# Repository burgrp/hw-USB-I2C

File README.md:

# USB-I2C bridge

USB to I2C bridge implemented on ESP32-C3FN4 MCU.

## Features

- Serial to I2C interface
- Alert line
- 3.3V, 5V power supply
- Simple serial protocol
- Implemented in MicroPython
- Designed in KiCAD

## Connectors

All connectors have the same pin-out as follows.

1. GND
2. SCL
3. SDA
4. +3.3 V
5. +5V
6. ALERT (IRQ)

## Binding

For Node.js there is a library [i2c-js](https://github.com/burgrp/i2c-js) published on NPM as [@burgrp/i2c](https://www.npmjs.com/package/@burgrp/i2c).

## USB protocol

- VID: 303A
- PID: 1001

The bridge is controlled through serial port by simple text protocol:

- `S` scans bus for devices, replies `Saddr1,addr2,addr3,...`
- `R,addr,len` reads data from device, replies `R,hex_data`
- `W,addr,hex_data` writes data to device, replies `W,acked_count`
- `A` gets alert line status, replies `AT` (true) or `AF` (false).

Addresses are always expressed in 7bit format, therefore without R/W bit.

### Example

By commands `S`, `R,79,2`, `A` we can scan the bus, read temperature from LM75A sensor found on address 79 and check the alert line:

```
> miniterm /dev/ttyACM0 115200 --raw
--- Miniterm on /dev/ttyACM0  115200,8,N,1 ---
--- Quit: Ctrl+] | Menu: Ctrl+T | Help: Ctrl+T followed by Ctrl+H ---
S
S79
R,79,2
R1A40
A
AF
```

## License
This work is licensed under a Creative Commons Attribution-ShareAlike 4.0 International License.

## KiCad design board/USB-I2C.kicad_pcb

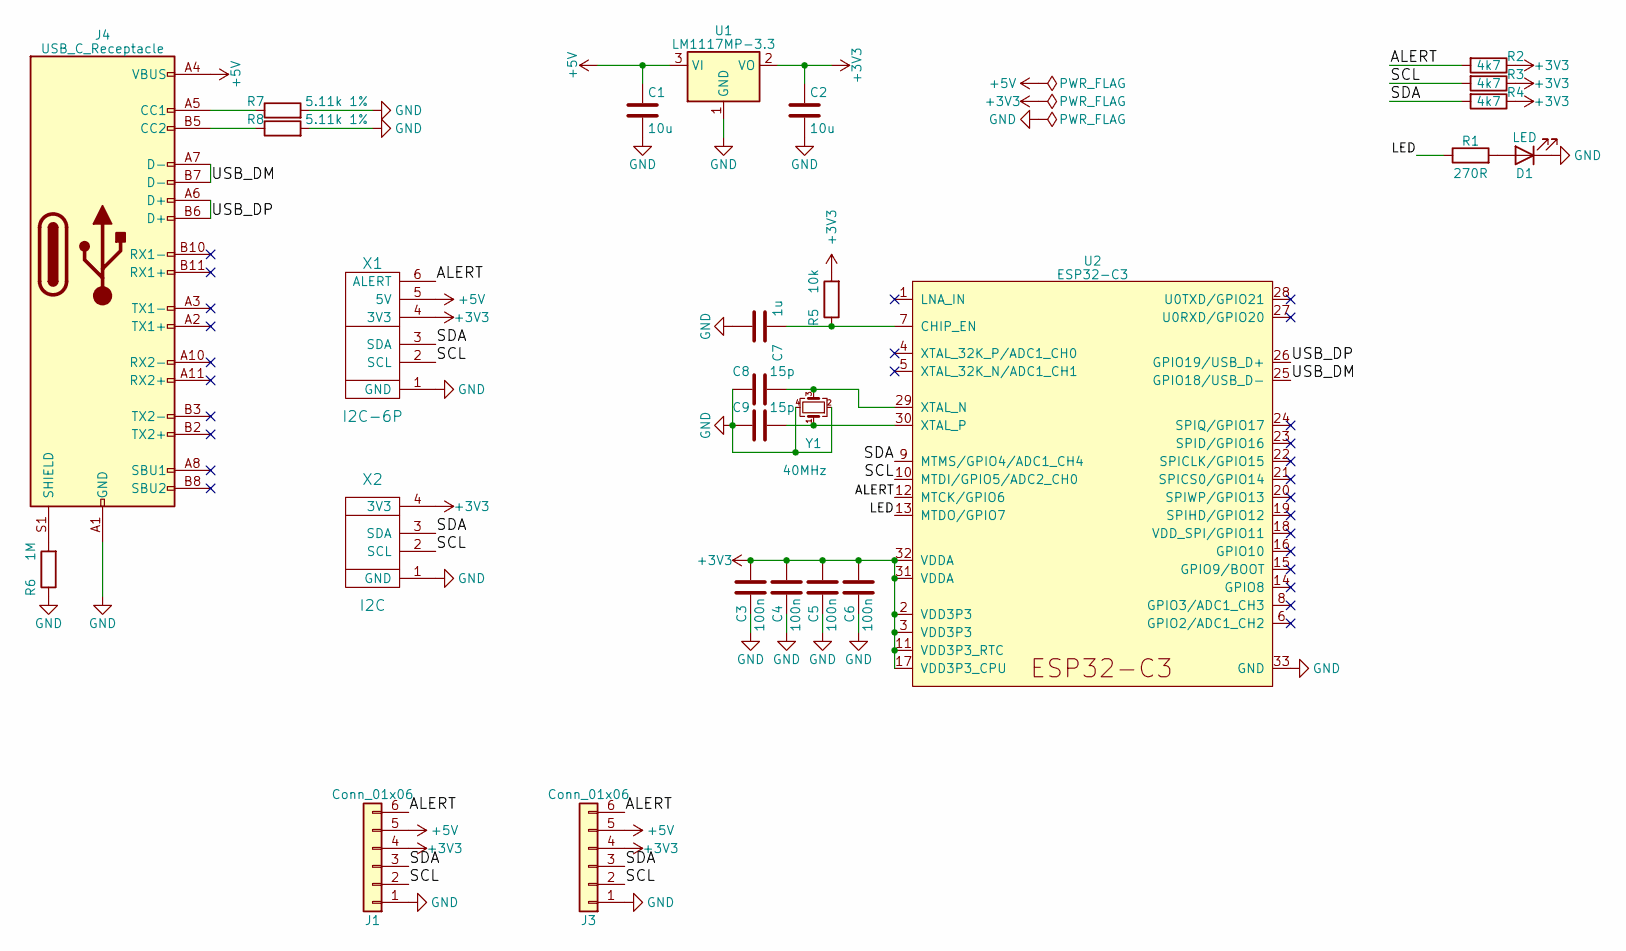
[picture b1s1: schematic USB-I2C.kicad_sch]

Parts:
C1, C2: 10u; C_0805_2012Metric
C3, C4, C5, C6: 100n; C_0805_2012Metric
C7: 1u; C_0805_2012Metric
C8, C9: 15p; C_0805_2012Metric
D1: LED; LED_0805_2012Metric
J1: Conn_01x06; PinHeader_1x06_P2.54mm_Vertical
J3: Conn_01x06; IDC-Header_2x03_P2.54mm_Vertical
J4: USB_C_Receptacle; USB_C_Receptacle_G-Switch_GT-USB-7010ASV
R1: 270R; R_0805_2012Metric
R2, R3, R4: 4k7; R_0805_2012Metric
R5: 10k; R_0805_2012Metric
R6: 1M; R_0805_2012Metric
R7, R8: 5.11k 1%; R_0805_2012Metric
U1: LM1117MP-3.3; SOT-223-3_TabPin2
U2: ESP32-C3; QFN-32-1EP_5x5mm_P0.5mm_EP3.45x3.45mm
X1: I2C-6P; Micro-Match-FOB-6
X2: I2C; Micro-Match-FOB-4
Y1: 40MHz; Crystal_SMD_3225-4Pin_3.2x2.5mm

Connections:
+3V3: C2.1, C3.1, C4.1, C5.1, C6.1, J1.4, J3.4, R2.1, R3.1, R4.1, R5.2, U1.2 (VO), U2.2 (VDD3P3), U2.3 (VDD3P3), U2.11 (VDD3P3_RTC), U2.17 (VDD3P3_CPU), U2.31 (VDDA), U2.32 (VDDA), X1.4 (3V3), X2.4 (3V3)
+5V: C1.1, J1.5, J3.5, J4.A4 (VBUS), J4.A9 (VBUS), J4.B4 (VBUS), J4.B9 (VBUS), U1.3 (VI), X1.5 (5V)
/ALERT: J1.6, J3.6, R2.2, U2.12 (MTCK/GPIO6), X1.6 (ALERT)
/LED: R1.1, U2.13 (MTDO/GPIO7)
/SCL: J1.2, J3.2, R3.2, U2.10 (MTDI/GPIO5/ADC2_CH0), X1.2 (SCL), X2.2 (SCL)
/SDA: J1.3, J3.3, R4.2, U2.9 (MTMS/GPIO4/ADC1_CH4), X1.3 (SDA), X2.3 (SDA)
/USB_DM: J4.A7 (D-), J4.B7 (D-), U2.25 (GPIO18/USB_D-)
/USB_DP: J4.A6 (D+), J4.B6 (D+), U2.26 (GPIO19/USB_D+)
GND: C1.2, C2.2, C3.2, C4.2, C5.2, C6.2, C7.1, C8.1, C9.1, D1.1 (K), J1.1, J3.1, J4.A1 (GND), J4.A12 (GND), J4.B1 (GND), J4.B12 (GND), R6.1, R7.2, R8.2, U1.1 (GND), U2.33 (GND), X1.1 (GND), X2.1 (GND), Y1.2, Y1.4
unnamed: D1.2 (A), R1.2
unnamed: J4.A5 (CC1), R7.1
unnamed: J4.B5 (CC2), R8.1
unnamed: J4.S1 (SHIELD), R6.2
unnamed: C7.2, R5.1, U2.7 (CHIP_EN)
unnamed: C8.2, U2.29 (XTAL_N), Y1.3
unnamed: C9.2, U2.30 (XTAL_P), Y1.1

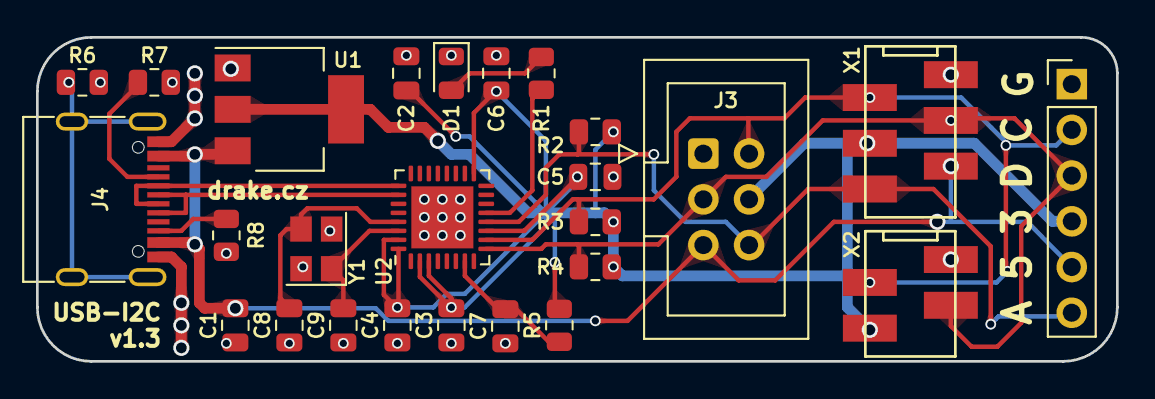
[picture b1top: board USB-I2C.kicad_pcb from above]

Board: 2 copper layers, 60.0 x 18.0 mm, 26 parts (0 on the bottom side), 16 nets.

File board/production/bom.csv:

Designator,Footprint,Quantity,Value,LCSC Part #
C1,0805,1,10u,
C2,0805,1,10u,
C3,0805,1,100n,
C4,0805,1,100n,
C5,0805,1,100n,
C6,0805,1,100n,
C7,0805,1,1u,
C8,0805,1,15p,
C9,0805,1,15p,
D1,0805,1,LED,
J1,PinHeader_1x06_P2.54mm_Vertical,1,Conn_01x06,
J3,IDC-Header_2x03_P2.54mm_Vertical,1,Conn_01x06,
J4,USB_C_Receptacle_G-Switch_GT-USB-7010ASV,1,USB_C_Receptacle,
R1,0805,1,270R,
R2,0805,1,4k7,
R3,0805,1,4k7,
R4,0805,1,4k7,
R5,0805,1,10k,
R6,0805,1,1M,
R7,0805,1,5.11k 1%,
R8,0805,1,5.11k 1%,
U1,SOT-223-3_TabPin2,1,LM1117MP-3.3,
U2,QFN-32-1EP_5x5mm_P0.5mm_EP3.45x3.45mm,1,ESP32-C3,
X1,Micro-Match-FOB-6,1,I2C-6P,
X2,Micro-Match-FOB-4,1,I2C,
Y1,Crystal_SMD_3225-4Pin_3.2x2.5mm,1,40MHz,

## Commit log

2020-09-02 Bump bl from 3.0.0 to 3.0.1 in /driver-js
    Bumps [bl](https://github.com/rvagg/bl) from 3.0.0 to 3.0.1.
    - [Release notes](https://github.com/rvagg/bl/releases)
    - [Commits](https://github.com/rvagg/bl/compare/v3.0.0...v3.0.1)
2020-12-11 Bump ini from 1.3.5 to 1.3.7 in /driver-js
    Bumps [ini](https://github.com/isaacs/ini) from 1.3.5 to 1.3.7.
    - [Release notes](https://github.com/isaacs/ini/releases)
    - [Commits](https://github.com/isaacs/ini/compare/v1.3.5...v1.3.7)
2023-06-08 Doc update
2026-01-02 Update IDF version and fix builder image variable order in Makefile
2026-03-12 Fix I2C frequency setting and update command structure in main.py
